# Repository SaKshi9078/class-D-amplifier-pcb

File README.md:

# Class D Amplifier PCB Design

This repository contains the complete design of a Class D Audio Amplifier
designed using KiCad.

## Project Overview
The project demonstrates the design flow of a Class D amplifier including
schematic design, PCB layout, and Gerber generation.

## Tools Used
- KiCad (Schematic & PCB Design)
- LTspice (Circuit Simulation)

## Files Included
- Schematic file (.kicad_sch)
- PCB layout file (.kicad_pcb)
- Gerber files for PCB manufacturing

## Description
The Class D amplifier uses an op-amp based comparator and MOSFET switching
stage. An LC filter is used at the output to recover the amplified audio signal.

## Author
Sakshi Anand Hawaldar

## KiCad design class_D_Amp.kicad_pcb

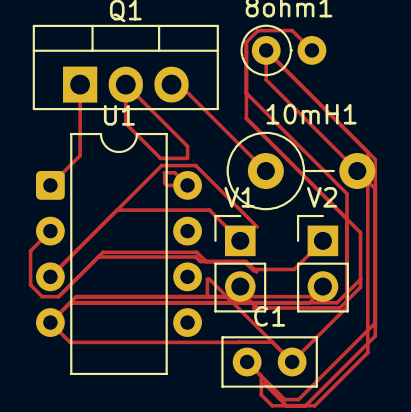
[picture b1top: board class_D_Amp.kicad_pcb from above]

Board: 2 copper layers, 7 parts (0 on the bottom side), 7 nets.

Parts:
8ohm1: R; R_Axial_DIN0207_L6.3mm_D2.5mm_P2.54mm_Vertical
10mH1: L; L_Axial_L9.5mm_D4.0mm_P5.08mm_Vertical_Fastron_SMCC
C1: C; C_Disc_D5.0mm_W2.5mm_P2.50mm
Q1: Q_NMOS_GDS; TO-220-3_Vertical
U1: LM358; CERDIP-8_W7.62mm_SideBrazed
V1: 12; PinHeader_1x02_P2.54mm_Vertical
V2: 1; PinHeader_1x02_P2.54mm_Vertical

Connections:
+12V: Q1.2 (D), U1.8 (V+)
GND: 8ohm1.2, C1.2, U1.4 (V-), V1.2, V2.2
unnamed: 8ohm1.1, 10mH1.2, C1.1
unnamed: Q1.1 (G), U1.1
unnamed: 10mH1.1, Q1.3 (S)
unnamed: U1.3 (+), V1.1
unnamed: U1.2 (-), V2.1

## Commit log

2026-01-31 Add README for Class D Amplifier PCB Design project
